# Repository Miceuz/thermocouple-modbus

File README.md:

thermocouple-modbus
===================

Thermocouple frontend accessible via industrial modbus protocol

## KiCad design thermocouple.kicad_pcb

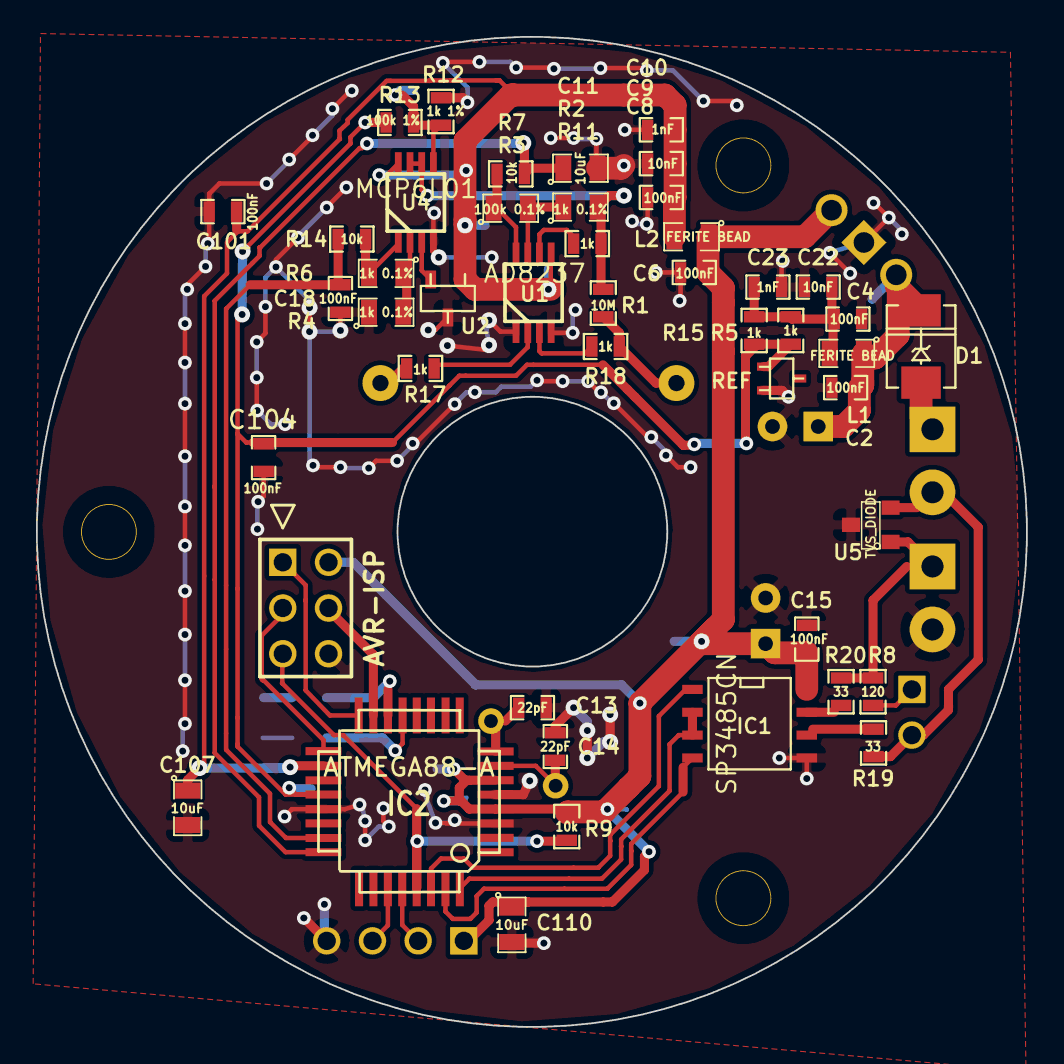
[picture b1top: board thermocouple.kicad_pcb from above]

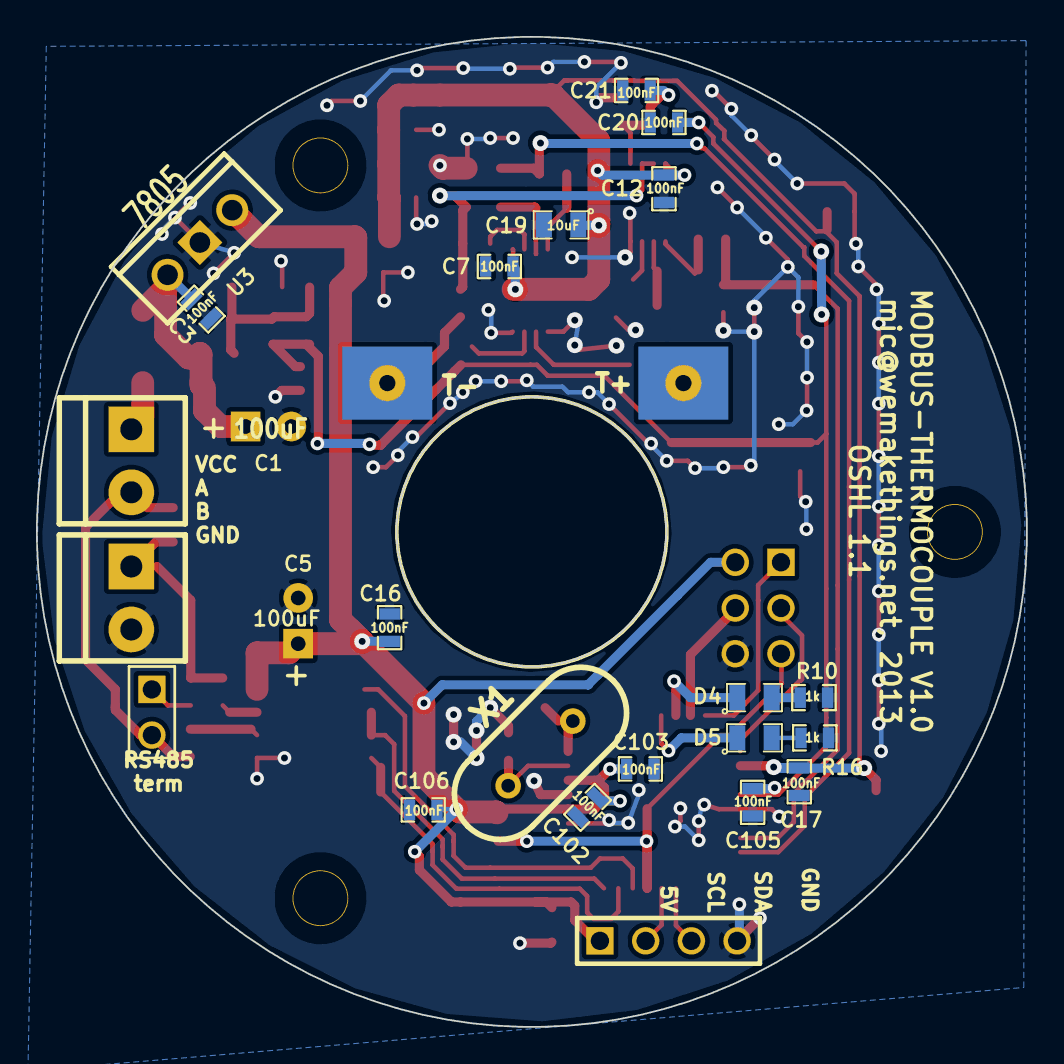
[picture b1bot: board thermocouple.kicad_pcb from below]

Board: 2 copper layers, 55.0 x 55.0 mm, 68 parts (22 on the bottom side), 37 nets.

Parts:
AVR-ISP: AVR-ISP-6; pin_array_3x2
C1, C5: 100uF; C1V8
C2, C3, C4, C6, C7, C8, C12, C15, C16, C17, C18, C20, C21, C101, C102, C103, C104, C105, C106: 100nF; SM0603_Capa
C9, C22: 10nF; SM0603_Capa
C10, C23: 1nF; SM0603_Capa
C11, C19, C107, C110: 10uF; SM0805
C13, C14: 22pF; SM0603_Capa
D1: DO-214AA(SMB)
D4, D5: SM0805
IC1: SP3485CN; SO8N
IC2: ATMEGA88-A; TQFP32
L1, L2: FERITE BEAD; SM0805
R1: 10M; SM0603_Resistor
R2, R4, R6: 1k 0.1%; SM0805
R3: 100k 0.1%; SM0805
R5, R10, R11, R15, R16, R17, R18: 1k; SM0603_Resistor
R7, R9, R14: 10k; SM0603_Resistor
R8: 120; SM0603_Resistor
R12: 1k 1%; SM0603_Resistor
R13: 100k 1%; SM0603_Resistor
R19, R20: 33; SM0603_Resistor
REF: ADR5045; sc70
T+: 1PIN_SMD
T-: 1PIN_SMD
U1: AD8237; MSOP_8
U2: TC1047; sot23
U3: 7805; LM78XXV
U4: MCP6L01; MSOP_8
U5: TVS_DIODE; SOT23
X1: HC-49V

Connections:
//RE: IC1.2, IC1.3, IC2.32
/A: R19.1, U5.2
/AMBIENT_TEMP: C18.1, IC2.23, R14.2
/AREF: C20.1, C104.1, C105.1, IC2.20, R5.1, R13.2, R15.1, REF.1
/B: R8.2, R20.1, U5.1
/FB: R2.1, R3.2, U1.7
/MISO: AVR-ISP.1, IC2.16
/MOSI: AVR-ISP.4, IC2.15
/RESET: AVR-ISP.5, IC2.29, R9.2
/RX: IC1.1, IC2.30
/SCK: AVR-ISP.3, IC2.17
/THERMOCOUPLE+: R17.1, T+.1
/THERMOCOUPLE-: R1.1, R18.1, T-.1, T-.2
/TX: IC1.4, IC2.31
/VTHERMO_FILTERED: C11.1, IC2.24, R7.2
GND: AVR-ISP.6, C1.2, C2.2, C3.2, C4.2, C5.2, C6.2, C7.2, C8.2, C9.2, C10.2, C11.2, C12.2, C13.2, C14.2, C15.2, C16.2, C17.2, C18.2, C19.2, C20.2, C21.2, C22.2, C23.2, C101.2, C102.2, C103.2, C104.2, C105.2, C106.2, C107.2, C110.2, IC1.5, IC2.3, IC2.5, IC2.21, R4.1, R10.2, R12.1, R16.2, REF.2, U1.1, U1.4, U2.3, U3.GND, U4.4, U5.3
unnamed: D4.2, R10.1
unnamed: D5.2, R16.1
unnamed: R17.2, U1.2
unnamed: C21.1, R12.2, R13.1, U4.5
unnamed: R6.2, R14.1, U4.1
unnamed: R4.2, R6.1, U4.2
unnamed: R18.2, U1.3
unnamed: R11.1, U1.6
unnamed: D4.1, IC2.14
unnamed: D5.1, IC2.13
unnamed: R1.2, R2.2, R11.2, U4.6, U4.7
unnamed: IC1.7, R20.2
unnamed: IC1.6, R19.2
unnamed: C13.1, IC2.8, X1.2
unnamed: C14.1, IC2.7, X1.1
unnamed: R3.1, R7.1, U1.8
unnamed: U2.2, U4.3
unnamed: C4.1, C22.1, C23.1, L1.2, R5.2, R15.2
VAA: C7.1, C8.1, C9.1, C10.1, C12.1, C17.1, C19.1, C101.1, C107.1, IC2.18, L2.2, U1.5, U2.1, U4.8
VCC: C1.1, C2.1, C3.1, D1.2, L1.1, U3.VI
VDD: AVR-ISP.2, C5.1, C6.1, C15.1, C16.1, C102.1, C103.1, C106.1, C110.1, IC1.8, IC2.4, IC2.6, L2.1, R9.1, U3.VO

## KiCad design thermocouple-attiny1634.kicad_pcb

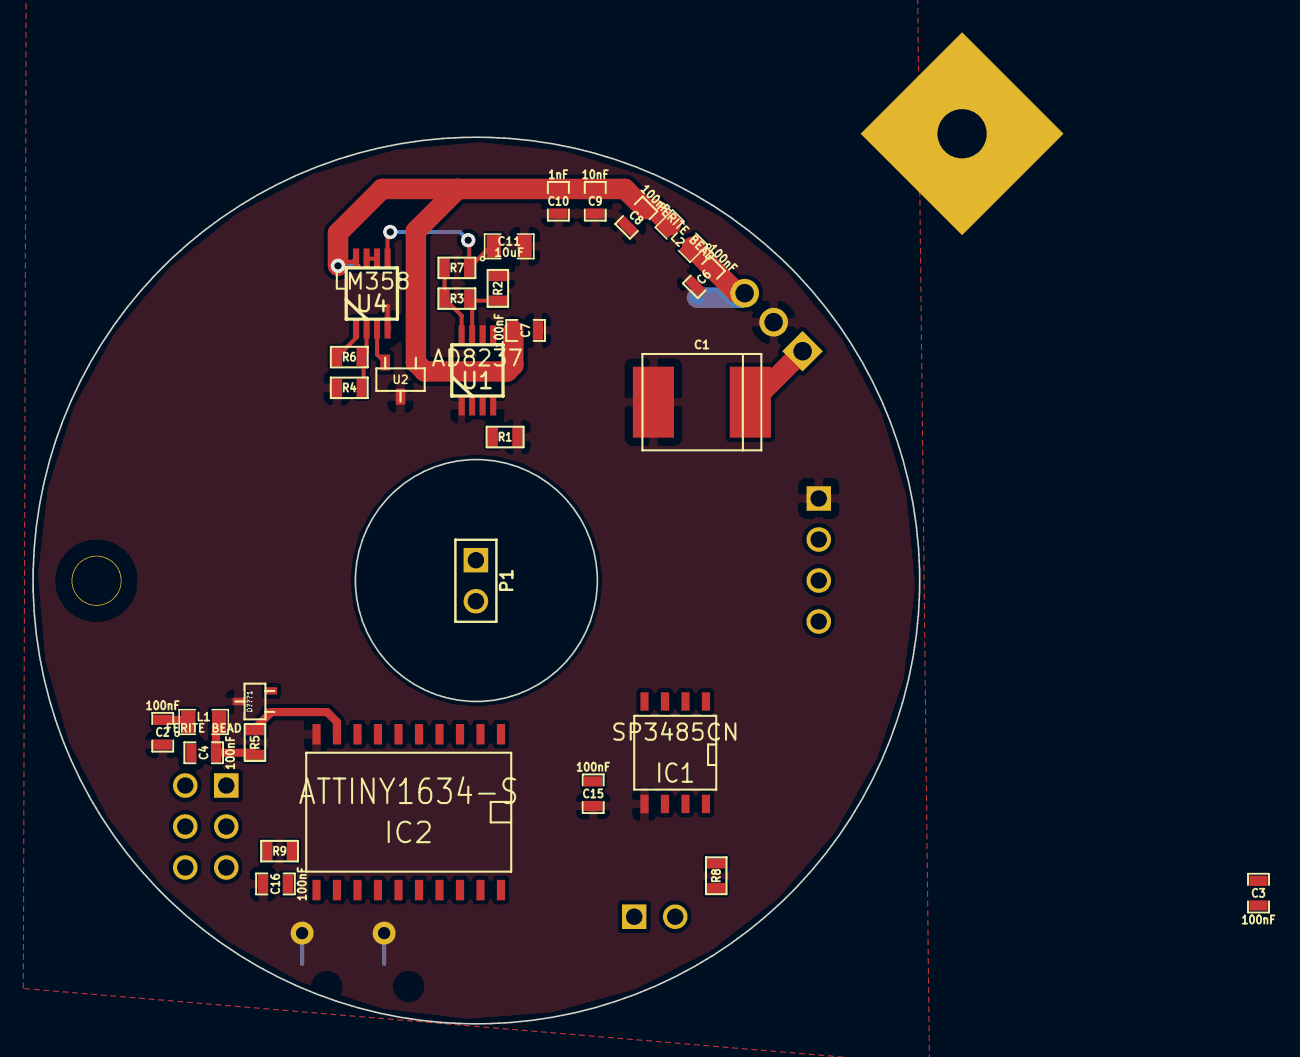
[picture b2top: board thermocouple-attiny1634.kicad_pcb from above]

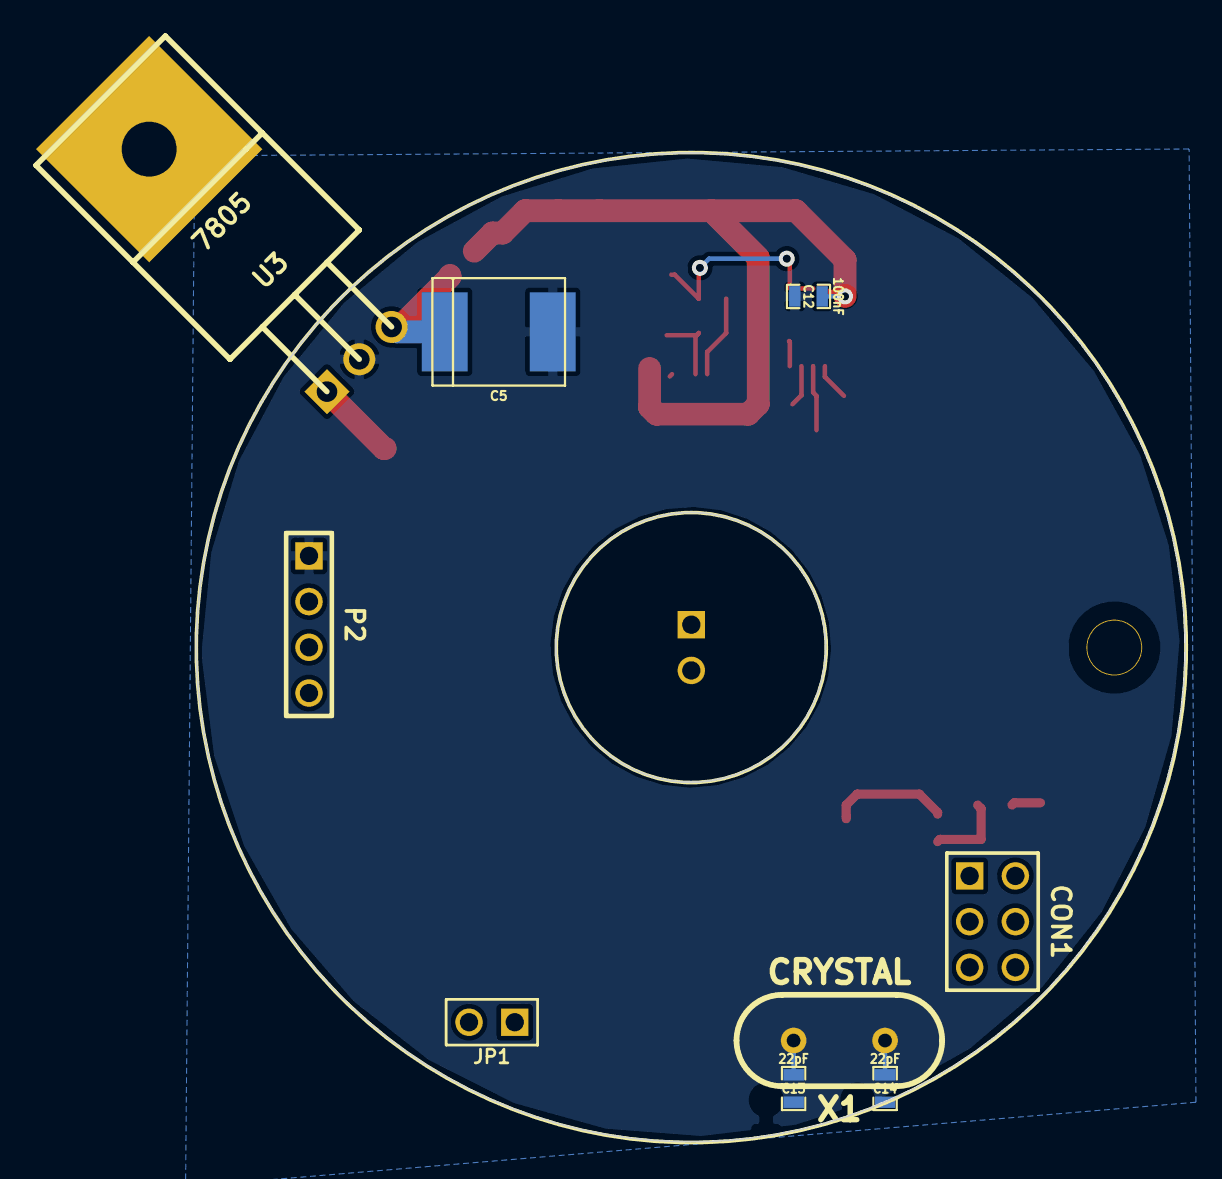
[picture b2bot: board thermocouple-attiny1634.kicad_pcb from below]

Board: 2 copper layers, 54.9 x 54.9 mm, 39 parts (9 on the bottom side), 24 nets.

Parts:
C1, C5: 100uF; c_tant_E
C2, C3, C4, C6, C7, C8, C12, C15, C16: 100nF; SM0603_Capa
C9: 10nF; SM0603_Capa
C10: 1nF; SM0603_Capa
C11: 10uF; SM0805
C13, C14: 22pF; SM0603_Capa
CON1: AVR-ISP-6; pin_array_3x2
D???1: ADR5045; sc70
IC1: SP3485CN; SO8N
IC2: ATTINY1634-S; SO20L
JP1: JUMPER; PIN_ARRAY_2X1
L1, L2: FERITE BEAD; SM0805
P1: CONN_2; PIN_ARRAY_2X1
P2: CONN_4; PIN_ARRAY_4x1
R1: 10M; SM0603
R2, R3, R5: R; SM0603
R4, R6: 1k; SM0603
R7: 10k; SM0603
R8, R9: 120; SM0603
U1: AD8237; MSOP_8
U2: TC1047; sot23
U3: 7805; TO220
U4: LM358; MSOP_8
X1: CRYSTAL; HC-49V

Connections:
//RE: IC1.2, IC1.3, IC2.3
/A: IC1.6, JP1.2, P2.3
/AMBIENT_TEMP: IC2.6, R6.2, U4.1
/AREF: D???1.1, IC2.9, R5.1
/B: IC1.7, P2.2, R8.2
/FB: R2.2, R3.2, U1.7
/RX: IC1.1, IC2.2
/TERMINATOR: JP1.1, R8.1
/THERMOCOUPLE+: P1.2, U1.2
/THERMOCOUPLE-: P1.1, R1.1, U1.3
/TX: IC1.4, IC2.1
/VTHERMO_BUFFERED: IC2.5, U4.6, U4.7
/VTHERMO_FILTERED: C11.1, R7.2, U4.5
GND: C1.2, C2.2, C3.2, C4.2, C5.2, C6.2, C7.2, C8.2, C9.2, C10.2, C11.2, C12.2, C13.2, C14.2, C15.2, C16.2, D???1.2, IC1.5, IC2.10, P2.1, R1.2, R2.1, R4.1, U1.1, U1.4, U1.6, U2.3, U3.2, U3.4, U4.4
unnamed: R4.2, R6.1, U4.2
unnamed: IC2.14, R9.1
unnamed: C4.1, L1.2, R5.2
unnamed: C13.1, IC2.13, X1.2
unnamed: C14.1, IC2.12, X1.1
unnamed: U2.2, U4.3
unnamed: R3.1, R7.1, U1.8
VAA: C7.1, C8.1, C9.1, C10.1, C12.1, L2.2, U1.5, U2.1, U4.8
VCC: C1.1, C2.1, C3.1, L1.1, P2.4, U3.1
VDD: C5.1, C6.1, C15.1, C16.1, IC2.11, L2.1, R9.2, U3.3

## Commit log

2013-05-12 initial
2013-05-18 visko daug
2013-05-18 and mechanical drawings? and mechanical drawings.
2013-05-23 blah
2013-05-24 suddenly everything went better than expected
2013-05-25 almost there
2013-05-26 RS485 protection added
2013-05-26 more stuff
2013-06-10 still fiddling around
2013-10-27 testing and calibration was going on
2014-01-20 some random test code
2014-04-01 temp table added, algorithm using interpolation, getting rid of floats and divisions, split up code to modules
2014-04-02 Tune up fixed point calculation constants to get max accuracy
2014-04-02 add more fixed point math comments
2014-04-02 remove binaries
2014-04-21 add I2C master driver from RP6 project
2014-04-21 set the correct clock speed in Makefile
2014-04-21 ok, we can speek to TriacBloc via I2C
2014-04-21 ant the naivest possible PID works
2014-04-22 slow pid setting
2014-04-22 more responsive controller
2014-04-23 clean up the code
2014-04-23 more fiddling around with code, test data saved
2014-04-27 Licence clause
2014-04-27 fiddle with naming
2014-04-27 don't sleep wile doing oversampled conversion as this starts conversion immedeately instead of respecting timing set up by tiemr0 compare match
2014-04-27 run timer in CTC mode, avoid manually reseting timer to 0. Now sampling frequency looks to be right
2014-04-27 run timer2 to generate triangle wave at frequency fsampling/16. this triangle wave is being added to measured signal
2014-04-28 PID library refactored
2014-04-28 refactor code a bit, extract adc to temperature conversion to separate function
2014-04-28 extract reader disable
2014-04-30 Basic ring buffer implementation
2014-05-01 add additional ADC read when reading without oversampling so that ADC settles after MUX change
2014-05-01 move simple methods to macros, bit of syntactic sugar, more tests
2014-05-01 interrupt based usart. note that ADC sleep nukes the ongoing transmission
2014-05-01 Fix grave bug where buffer was accessed asynchroneusly, switch read-enable off after every transmitted char in order to receive
2014-05-01 echo received char back
2014-05-01 add simple command line interface
2014-05-01 disable interrupts while accessing buffer which is accessed from interrupt
2014-05-01 use cli
